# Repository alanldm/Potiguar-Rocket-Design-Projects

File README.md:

# Potiguar-Rocket-Design-Projects
Meus trabalhos no projeto de extensão da UFRN Potiguar Rocket Design (PRD).

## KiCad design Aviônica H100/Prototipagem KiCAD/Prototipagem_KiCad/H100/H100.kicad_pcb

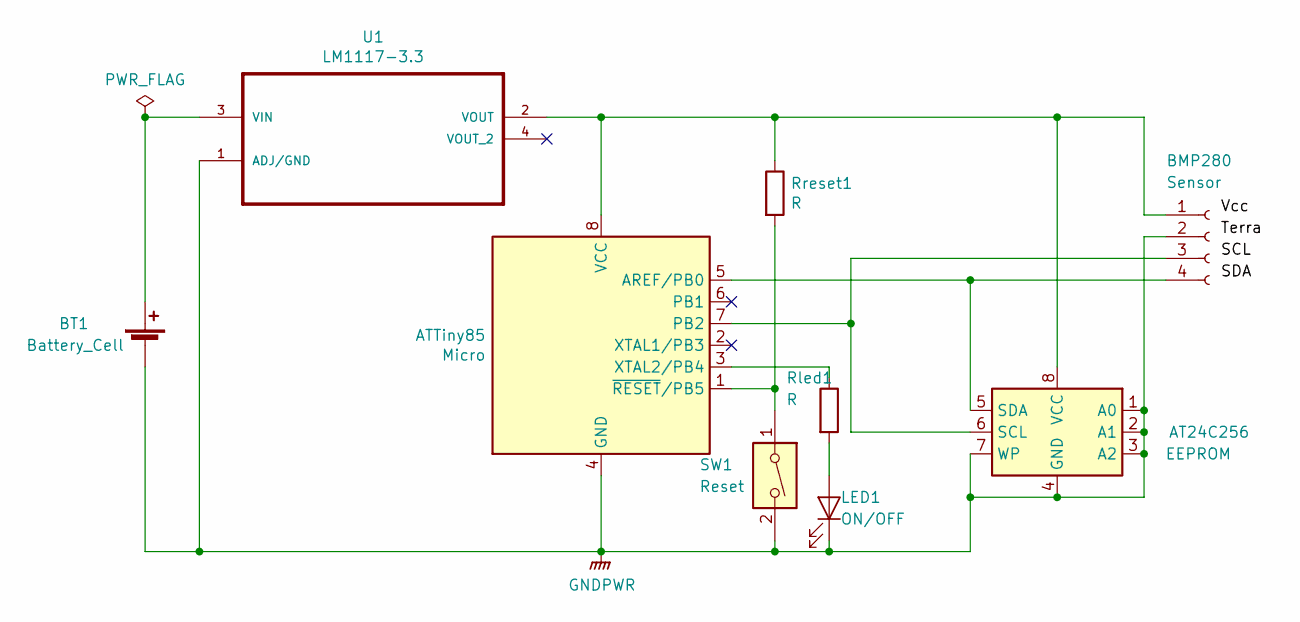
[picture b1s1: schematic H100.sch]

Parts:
AT24C256: EEPROM; DIP-8_W7.62mm_Socket
ATTiny85: Micro; DIP-8_W7.62mm_Socket
BMP280: Sensor; PinSocket_1x04_P2.54mm_Vertical
BT1: Battery_Cell; LR44
LED1: ON/OFF; LED_D3.0mm
Rled1: R; R_Axial_DIN0207_L6.3mm_D2.5mm_P2.54mm_Vertical
Rreset1: R; R_Axial_DIN0207_L6.3mm_D2.5mm_P2.54mm_Vertical
SW1: Reset; SW_PUSH_6mm_H5mm
U1: LM1117-3.3; SOT230

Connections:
GNDPWR: AT24C256.1 (A0), AT24C256.2 (A1), AT24C256.3 (A2), AT24C256.4 (GND), AT24C256.7 (WP), ATTiny85.4 (GND), BMP280.2, BT1.2 (-), LED1.1 (K), SW1.2, U1.1 (ADJ/GND)
unnamed: AT24C256.5 (SDA), ATTiny85.5 (AREF/PB0), BMP280.4
unnamed: AT24C256.6 (SCL), ATTiny85.7 (PB2), BMP280.3
unnamed: AT24C256.8 (VCC), ATTiny85.8 (VCC), BMP280.1, Rreset1.1, U1.2 (VOUT)
unnamed: ATTiny85.1 (~RESET~/PB5), Rreset1.2, SW1.1
unnamed: ATTiny85.3 (XTAL2/PB4), Rled1.1
unnamed: BT1.1 (+), U1.3 (VIN)
unnamed: LED1.2 (A), Rled1.2

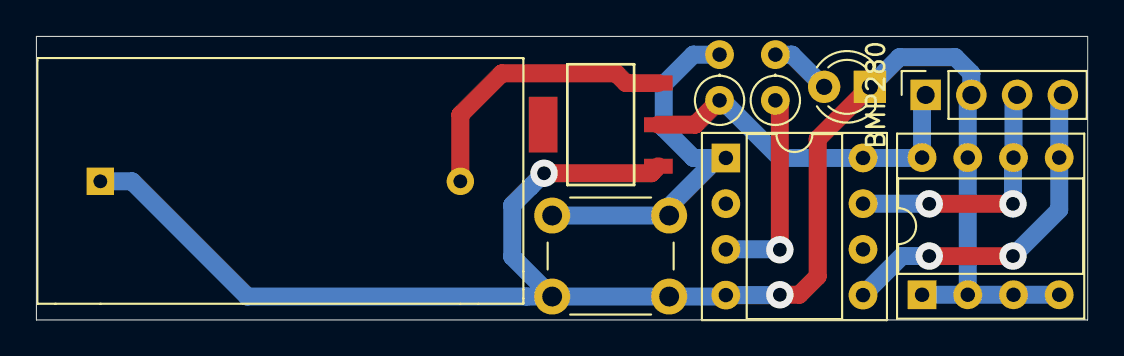
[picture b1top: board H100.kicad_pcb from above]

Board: 2 copper layers, 58.4 x 15.8 mm, 9 parts (0 on the bottom side), 8 nets.

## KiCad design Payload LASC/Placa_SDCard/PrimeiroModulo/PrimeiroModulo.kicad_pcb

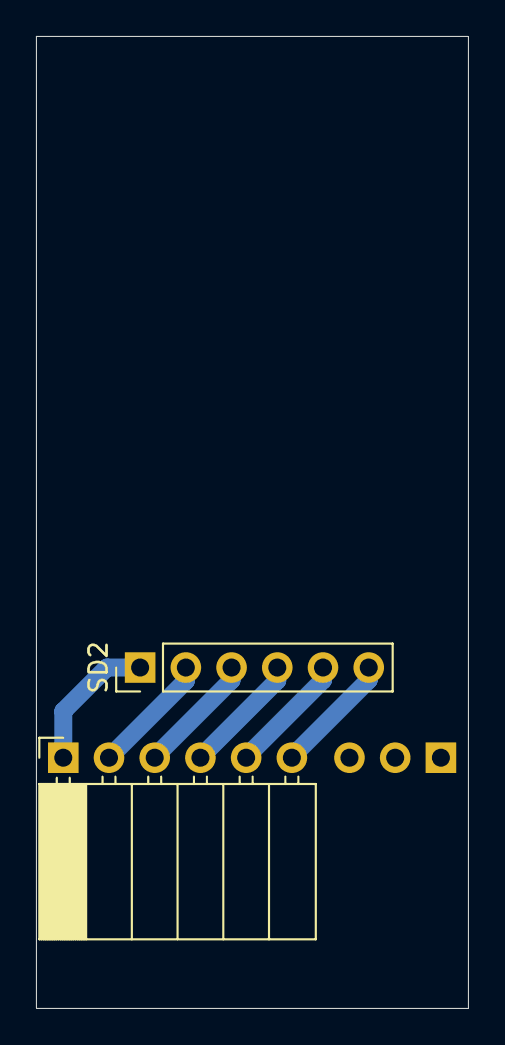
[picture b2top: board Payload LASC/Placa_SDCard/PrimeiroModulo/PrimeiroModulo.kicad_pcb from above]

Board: 2 copper layers, 24.0 x 54.0 mm, 3 parts (1 on the bottom side), 6 nets.

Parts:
SD1: Con; PinSocket_1x06_P2.54mm_Horizontal
SD2: Con; PinHeader_1x06_P2.54mm_Vertical
Supporte1: Con; PinSocket_1x03_P2.54mm_Horizontal

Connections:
CS: SD1.6, SD2.6
Gnd: SD1.1, SD2.1
MISO: SD1.3, SD2.3
MOSI: SD1.4, SD2.4
SCK: SD1.5, SD2.5
Vcc: SD1.2, SD2.2

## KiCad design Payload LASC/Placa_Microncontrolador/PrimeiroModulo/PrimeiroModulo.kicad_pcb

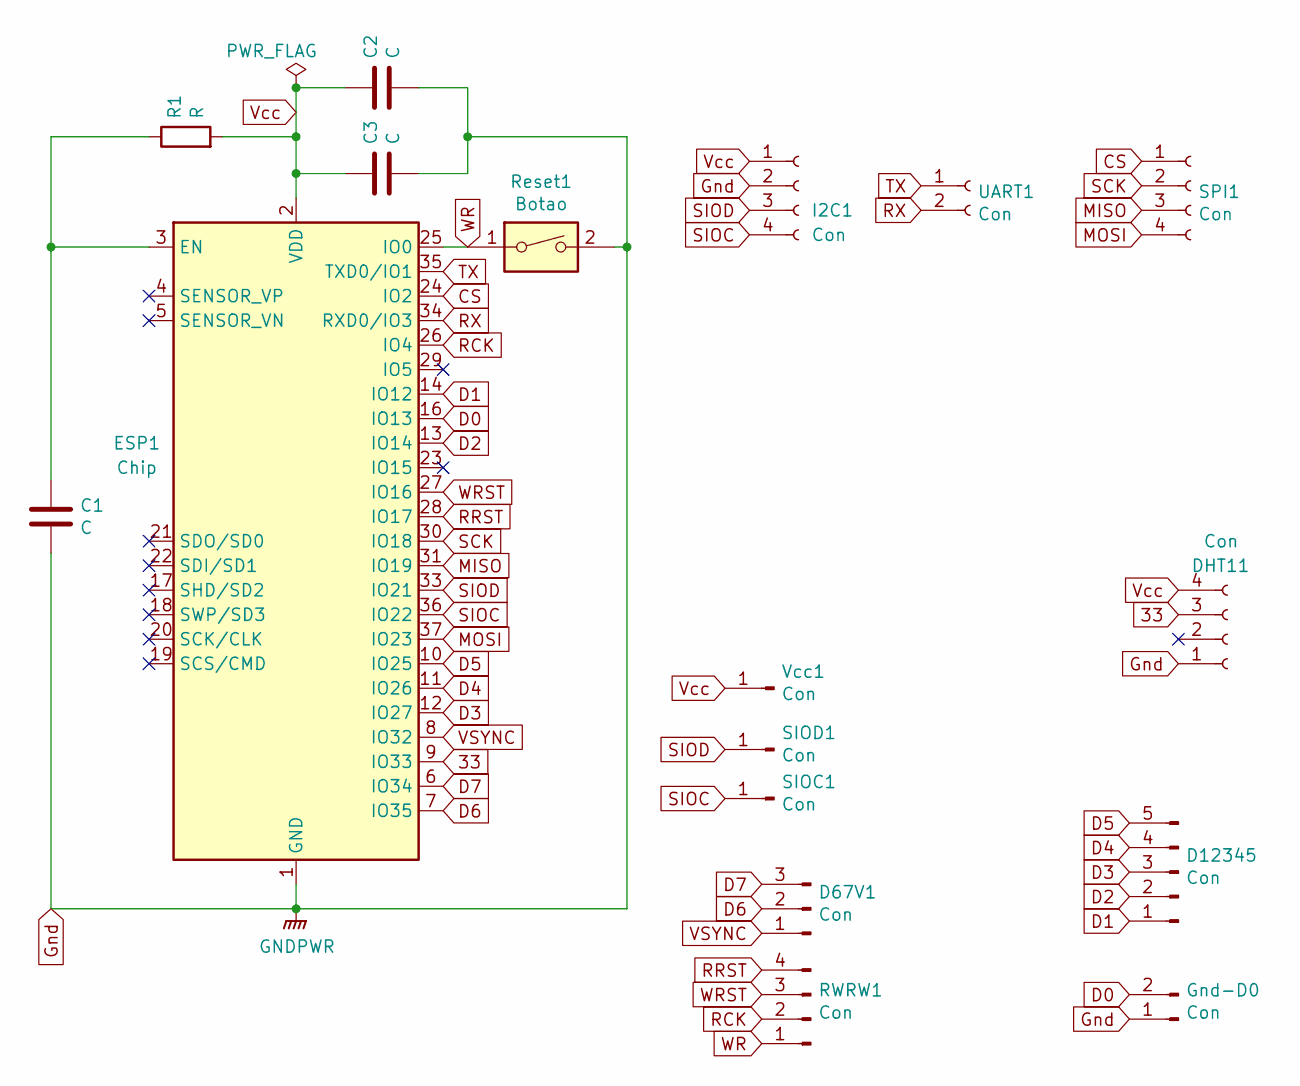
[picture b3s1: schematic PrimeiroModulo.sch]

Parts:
C1, C2: C; C_Disc_D5.1mm_W3.2mm_P5.00mm
C3: C; CP_Axial_L11.0mm_D5.0mm_P18.00mm_Horizontal
D67V1: Con; PinHeader_1x03_P2.54mm_Vertical
D12345: Con; PinHeader_1x05_P2.54mm_Vertical
DHT11: Con; PinSocket_1x04_P2.54mm_Horizontal
ESP1: Chip; ESP32-WROOM-32
Gnd-D0: Con; PinHeader_1x02_P2.54mm_Vertical
I2C1: Con; PinSocket_1x04_P2.54mm_Vertical
R1: R; R_Axial_DIN0204_L3.6mm_D1.6mm_P7.62mm_Horizontal
RWRW1: Con; PinHeader_1x04_P2.54mm_Vertical
Reset1: Botao; SW_PUSH_6mm
SIOC1: Con; PinHeader_1x01_P2.54mm_Vertical
SIOD1: Con; PinHeader_1x01_P2.54mm_Vertical
SPI1: Con; PinSocket_1x04_P2.54mm_Vertical
UART1: Con; PinSocket_1x02_P2.54mm_Vertical
Vcc1: Con; PinHeader_1x01_P2.54mm_Vertical

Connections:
33: DHT11.3, ESP1.9 (IO33)
CS: ESP1.24 (IO2), SPI1.1
D0: ESP1.16 (IO13), Gnd-D0.2
D1: D12345.1, ESP1.14 (IO12)
D2: D12345.2, ESP1.13 (IO14)
D3: D12345.3, ESP1.12 (IO27)
D4: D12345.4, ESP1.11 (IO26)
D5: D12345.5, ESP1.10 (IO25)
D6: D67V1.2, ESP1.7 (IO35)
D7: D67V1.3, ESP1.6 (IO34)
Gnd: C1.2, C2.2, C3.2, DHT11.1, ESP1.1 (GND), ESP1.15 (GND), ESP1.38 (GND), ESP1.39 (GND), Gnd-D0.1, I2C1.2, Reset1.2
MISO: ESP1.31 (IO19), SPI1.3
MOSI: ESP1.37 (IO23), SPI1.4
unnamed: C1.1, ESP1.3 (EN), R1.1
RCK: ESP1.26 (IO4), RWRW1.2
RRST: ESP1.28 (IO17), RWRW1.4
RX: ESP1.34 (RXD0/IO3), UART1.2
SCK: ESP1.30 (IO18), SPI1.2
SIOC: ESP1.36 (IO22), I2C1.4, SIOC1.1
SIOD: ESP1.33 (IO21), I2C1.3, SIOD1.1
TX: ESP1.35 (TXD0/IO1), UART1.1
VSYNC: D67V1.1, ESP1.8 (IO32)
Vcc: C2.1, C3.1, DHT11.4, ESP1.2 (VDD), I2C1.1, R1.2, Vcc1.1
WR: ESP1.25 (IO0), RWRW1.1, Reset1.1
WRST: ESP1.27 (IO16), RWRW1.3

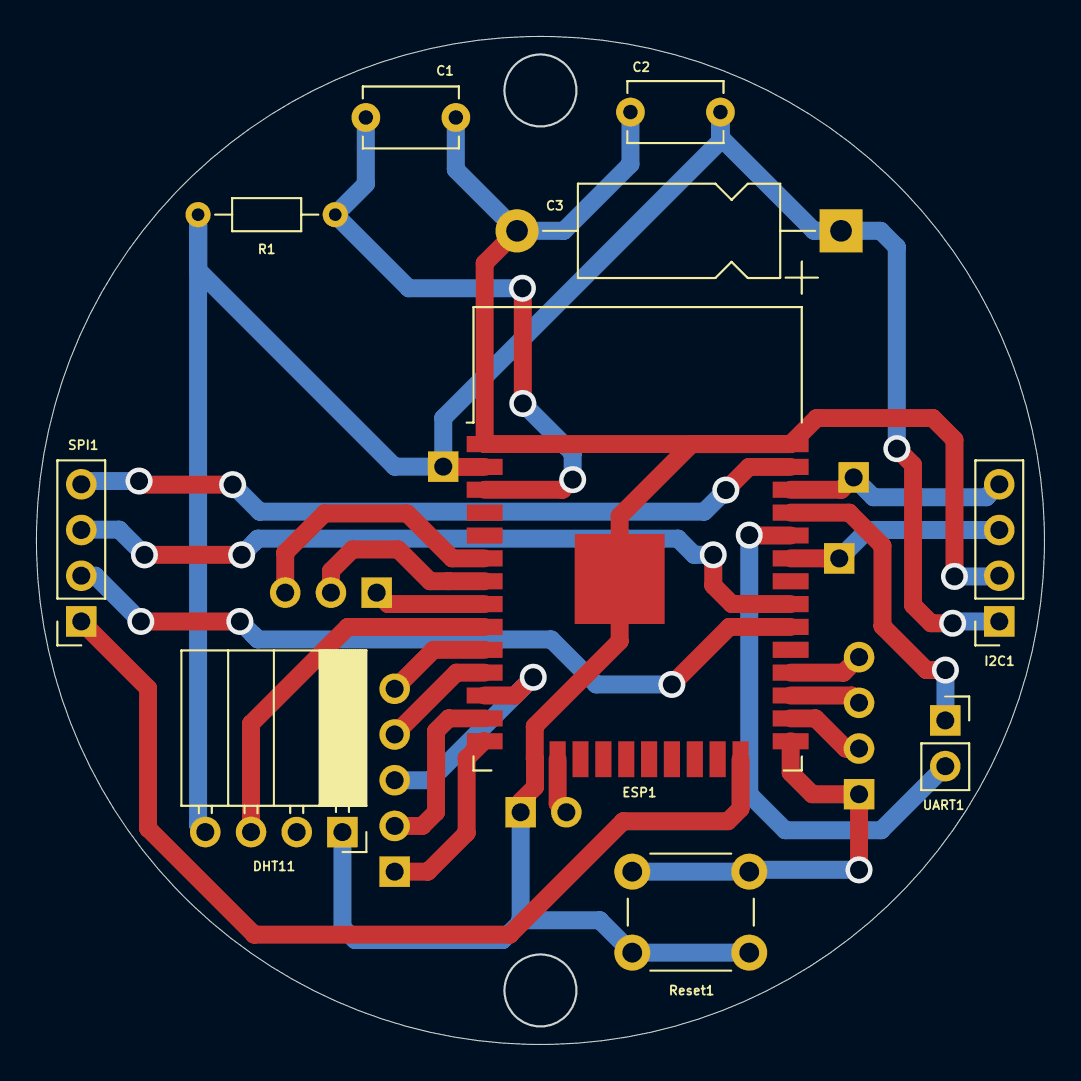
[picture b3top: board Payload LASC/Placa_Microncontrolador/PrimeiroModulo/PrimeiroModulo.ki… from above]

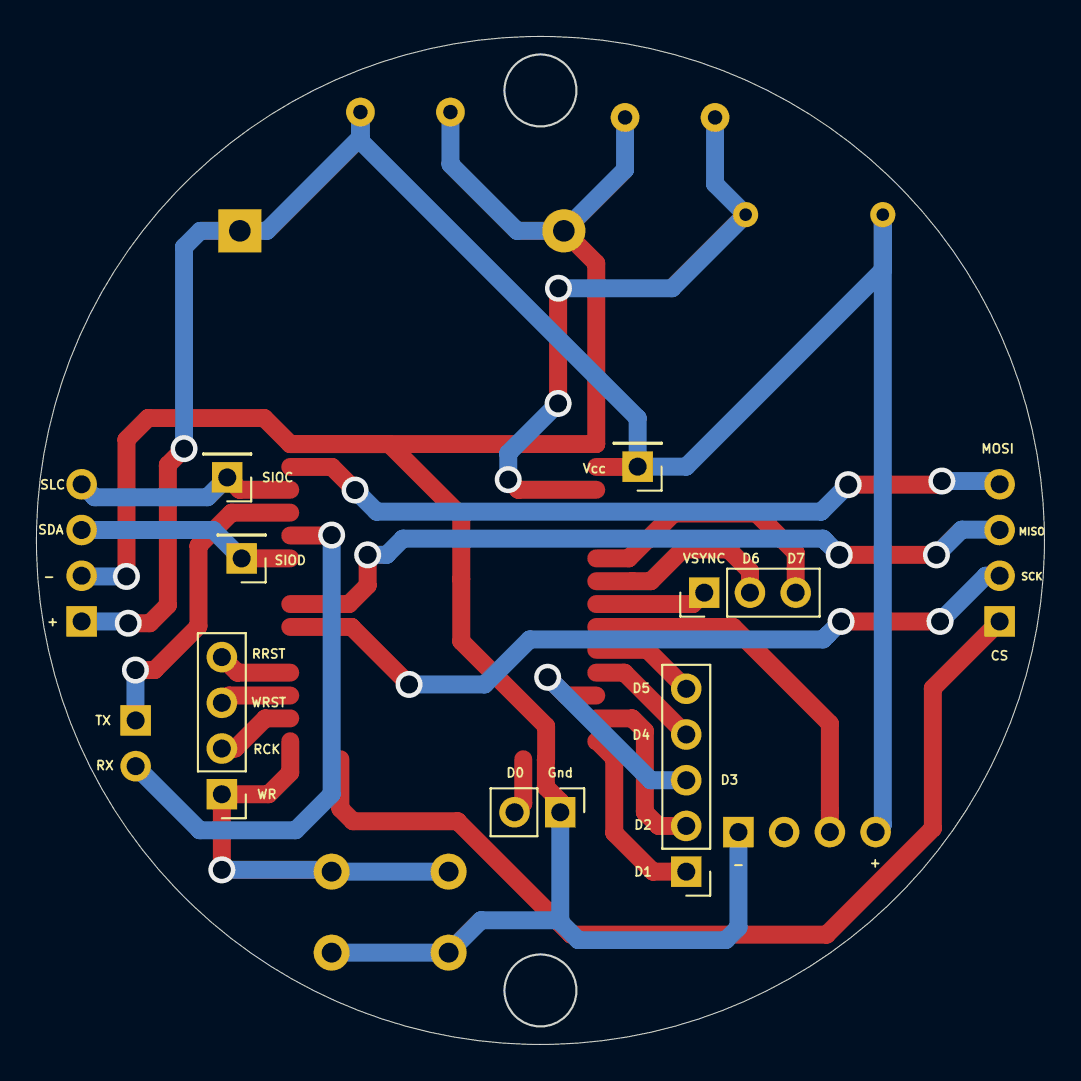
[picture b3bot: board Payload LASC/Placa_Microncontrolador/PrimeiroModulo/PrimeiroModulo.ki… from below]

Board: 2 copper layers, 55.9 x 55.9 mm, 17 parts (7 on the bottom side), 25 nets.

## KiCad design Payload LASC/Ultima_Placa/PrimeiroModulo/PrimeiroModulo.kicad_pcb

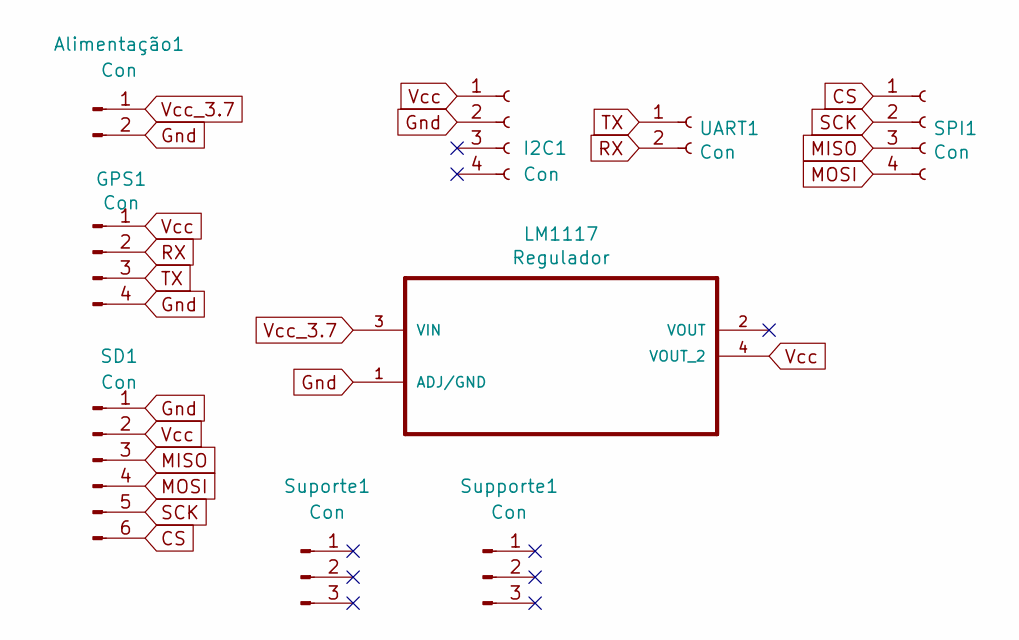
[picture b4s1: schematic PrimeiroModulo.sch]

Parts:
Alimentação1: Con; PinHeader_1x02_P2.54mm_Vertical
GPS1: Con; PinHeader_1x04_P2.54mm_Vertical
I2C1: Con; PinSocket_1x04_P2.54mm_Vertical
LM1117: Regulador; SOT230
SD1: Con; PinHeader_1x06_P2.54mm_Vertical
SPI1: Con; PinSocket_1x04_P2.54mm_Vertical
Suporte1: Con; PinHeader_1x03_P2.54mm_Vertical
Supporte1: Con; PinHeader_1x03_P2.54mm_Vertical
UART1: Con; PinSocket_1x02_P2.54mm_Vertical

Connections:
CS: SD1.6, SPI1.1
Gnd: Alimentação1.2, GPS1.4, I2C1.2, LM1117.1 (ADJ/GND), SD1.1
MISO: SD1.3, SPI1.3
MOSI: SD1.4, SPI1.4
RX: GPS1.2, UART1.2
SCK: SD1.5, SPI1.2
TX: GPS1.3, UART1.1
Vcc: GPS1.1, I2C1.1, LM1117.4 (VOUT_2), SD1.2
Vcc_3.7: Alimentação1.1, LM1117.3 (VIN)

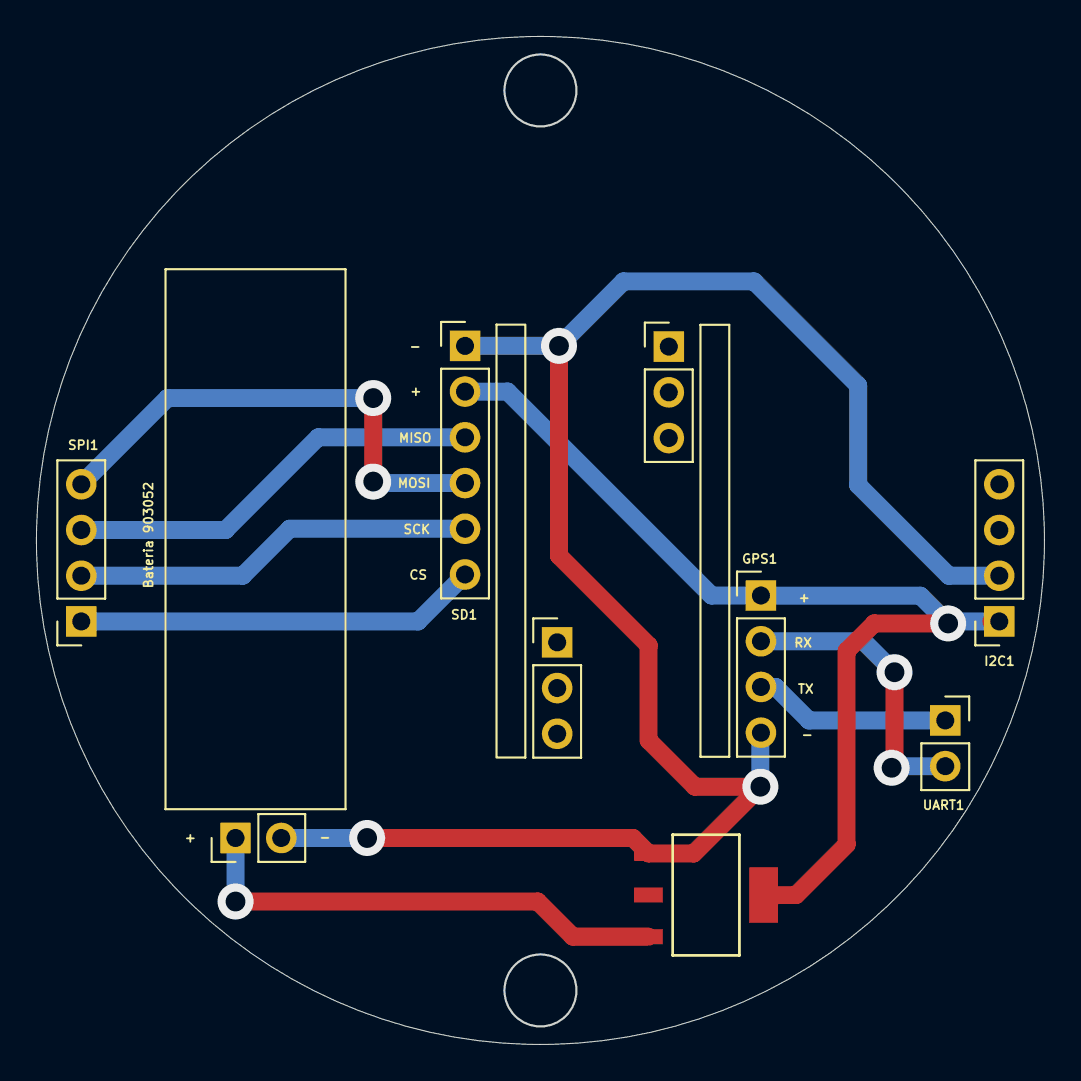
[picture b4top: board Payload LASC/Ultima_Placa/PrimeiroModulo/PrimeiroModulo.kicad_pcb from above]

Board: 2 copper layers, 55.9 x 55.9 mm, 9 parts (0 on the bottom side), 9 nets.

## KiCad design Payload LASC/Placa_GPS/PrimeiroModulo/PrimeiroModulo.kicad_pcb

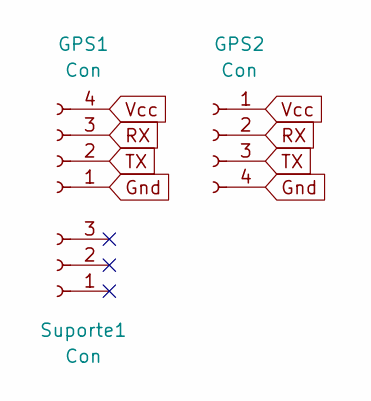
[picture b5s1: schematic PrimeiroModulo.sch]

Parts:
GPS1: Con; PinSocket_1x04_P2.54mm_Horizontal
GPS2: Con; PinHeader_1x04_P2.54mm_Vertical
Suporte1: Con; PinSocket_1x03_P2.54mm_Horizontal

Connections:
Gnd: GPS1.1, GPS2.4
RX: GPS1.3, GPS2.2
TX: GPS1.2, GPS2.3
Vcc: GPS1.4, GPS2.1

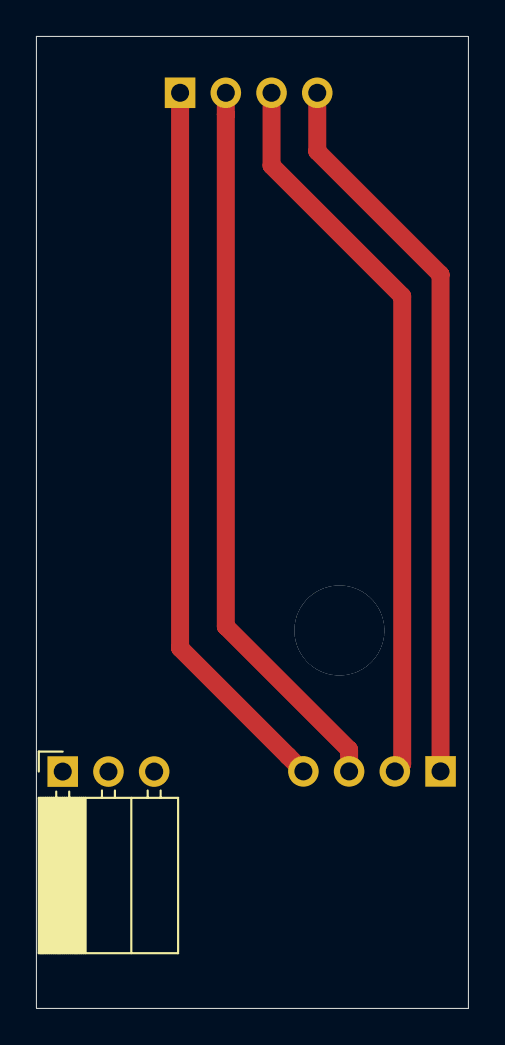
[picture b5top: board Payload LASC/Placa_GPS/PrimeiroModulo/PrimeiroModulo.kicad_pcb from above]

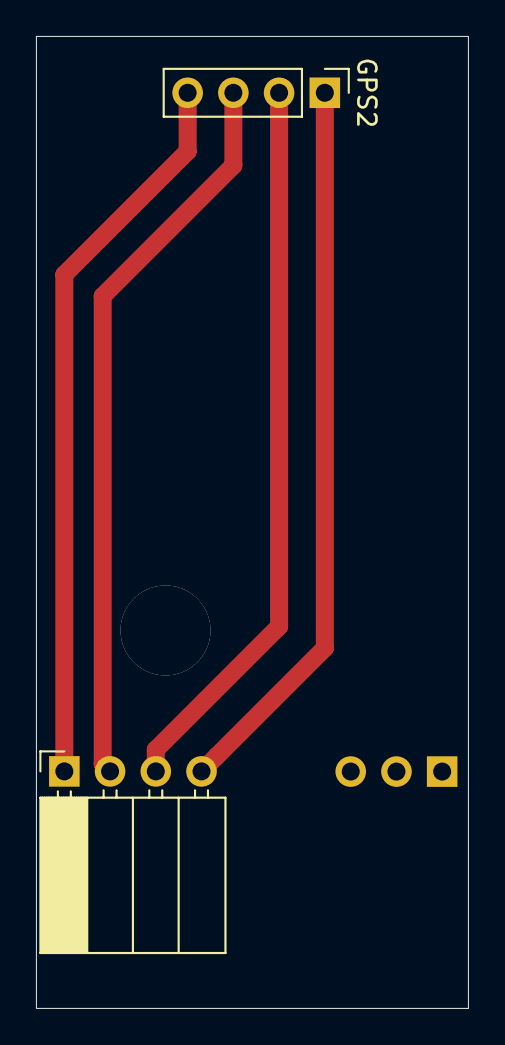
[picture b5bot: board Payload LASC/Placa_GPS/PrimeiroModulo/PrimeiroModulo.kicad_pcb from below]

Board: 2 copper layers, 24.0 x 54.0 mm, 3 parts (2 on the bottom side), 4 nets.

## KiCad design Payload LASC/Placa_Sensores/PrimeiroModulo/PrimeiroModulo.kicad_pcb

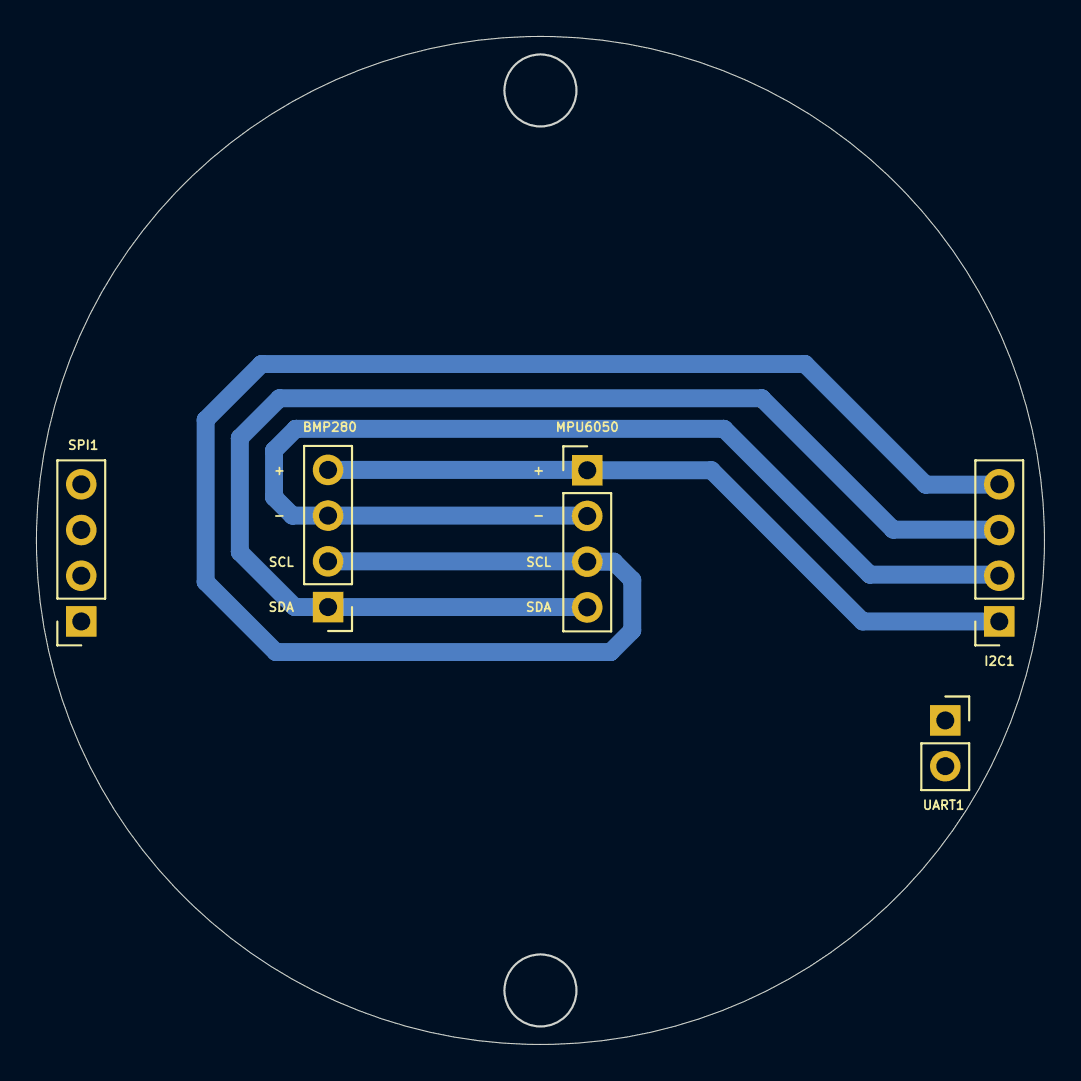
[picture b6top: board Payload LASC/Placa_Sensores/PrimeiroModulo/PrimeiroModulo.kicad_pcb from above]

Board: 2 copper layers, 55.9 x 55.9 mm, 5 parts (0 on the bottom side), 4 nets.

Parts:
BMP280: Con; PinHeader_1x04_P2.54mm_Vertical
I2C1: Con; PinSocket_1x04_P2.54mm_Vertical
MPU6050: Con; PinHeader_1x04_P2.54mm_Vertical
SPI1: Con; PinSocket_1x04_P2.54mm_Vertical
UART1: Con; PinSocket_1x02_P2.54mm_Vertical

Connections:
Gnd: BMP280.3, I2C1.2, MPU6050.2
SIOC: BMP280.2, I2C1.4, MPU6050.3
SIOD: BMP280.1, I2C1.3, MPU6050.4
Vcc: BMP280.4, I2C1.1, MPU6050.1

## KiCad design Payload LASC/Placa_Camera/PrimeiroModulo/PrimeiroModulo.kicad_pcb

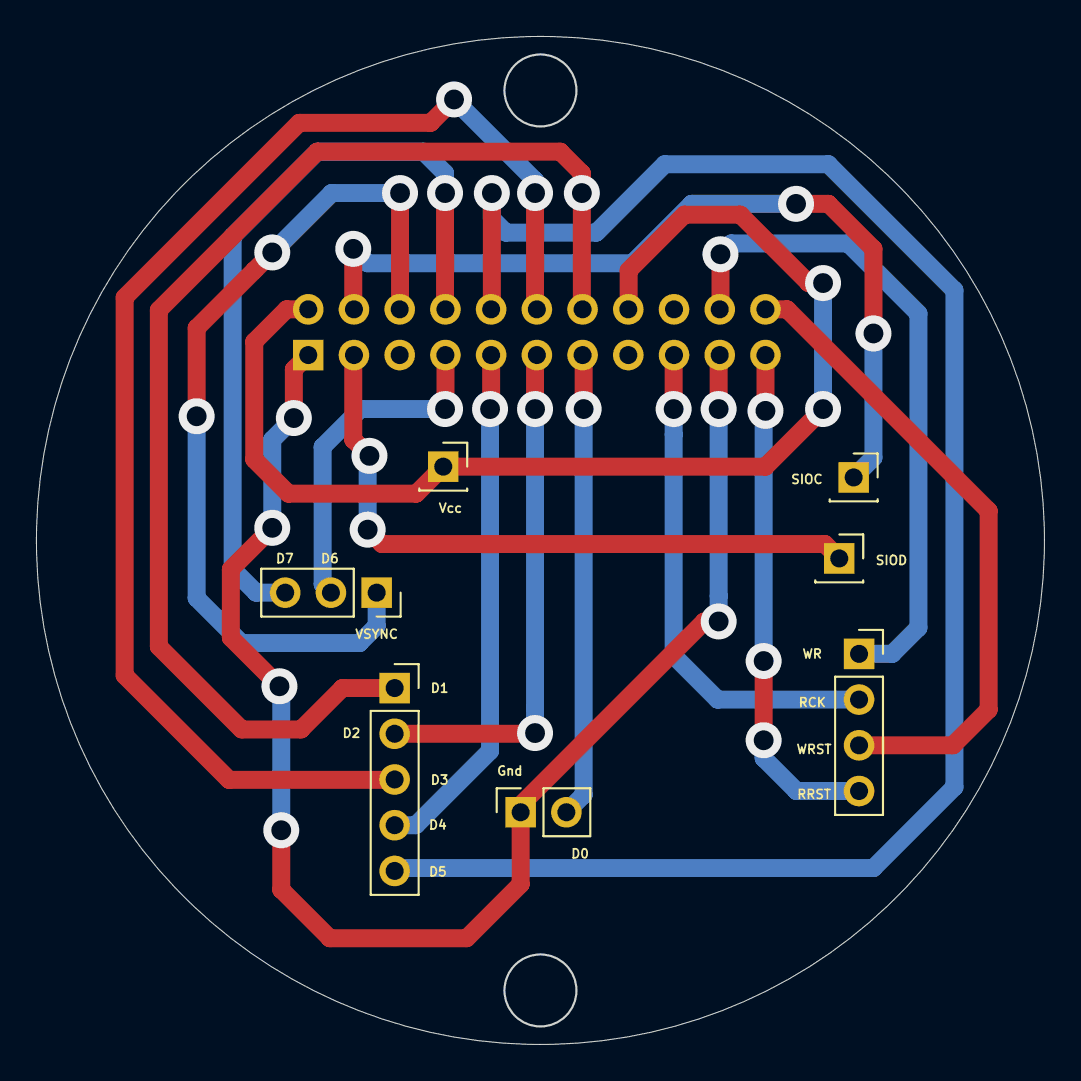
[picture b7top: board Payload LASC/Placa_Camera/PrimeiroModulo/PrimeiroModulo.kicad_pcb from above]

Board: 2 copper layers, 55.9 x 55.9 mm, 8 parts (1 on the bottom side), 17 nets.

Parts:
D67V1: Con; PinSocket_1x03_P2.54mm_Vertical
D12345: Con; PinSocket_1x05_P2.54mm_Vertical
Gnd-D0: Con; PinSocket_1x02_P2.54mm_Vertical
OV76: Con; PinSocket_2x11_P2.54mm_Vertical
RWRW1: Con; PinSocket_1x04_P2.54mm_Vertical
SIOC1: Con; PinSocket_1x01_P2.54mm_Vertical
SIOD1: Con; PinSocket_1x01_P2.54mm_Vertical
Vcc1: Con; PinSocket_1x01_P2.54mm_Vertical

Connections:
D0: Gnd-D0.2, OV76.13
D1: D12345.1, OV76.14
D2: D12345.2, OV76.11
D3: D12345.3, OV76.12
D4: D12345.4, OV76.9
D5: D12345.5, OV76.10
D6: D67V1.2, OV76.7
D7: D67V1.3, OV76.8
Gnd: Gnd-D0.1, OV76.1, OV76.19
RCK: OV76.17, RWRW1.2
RRST: OV76.21, RWRW1.4
SIOC: OV76.4, SIOC1.1
SIOD: OV76.3, SIOD1.1
VSYNC: D67V1.1, OV76.6
Vcc: OV76.2, OV76.16, Vcc1.1
WR: OV76.20, RWRW1.1
WRST: OV76.22, RWRW1.3

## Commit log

2020-11-25 Inserido meus projetos realizados na equipe
